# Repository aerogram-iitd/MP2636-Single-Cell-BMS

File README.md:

View this project on [CADLAB.io](https://cadlab.io/project/24484). 

# MP2636-Single-Cell-BMS
3A Switch Mode Battery Charger with System Boost using MP2636 from Monolithic Power

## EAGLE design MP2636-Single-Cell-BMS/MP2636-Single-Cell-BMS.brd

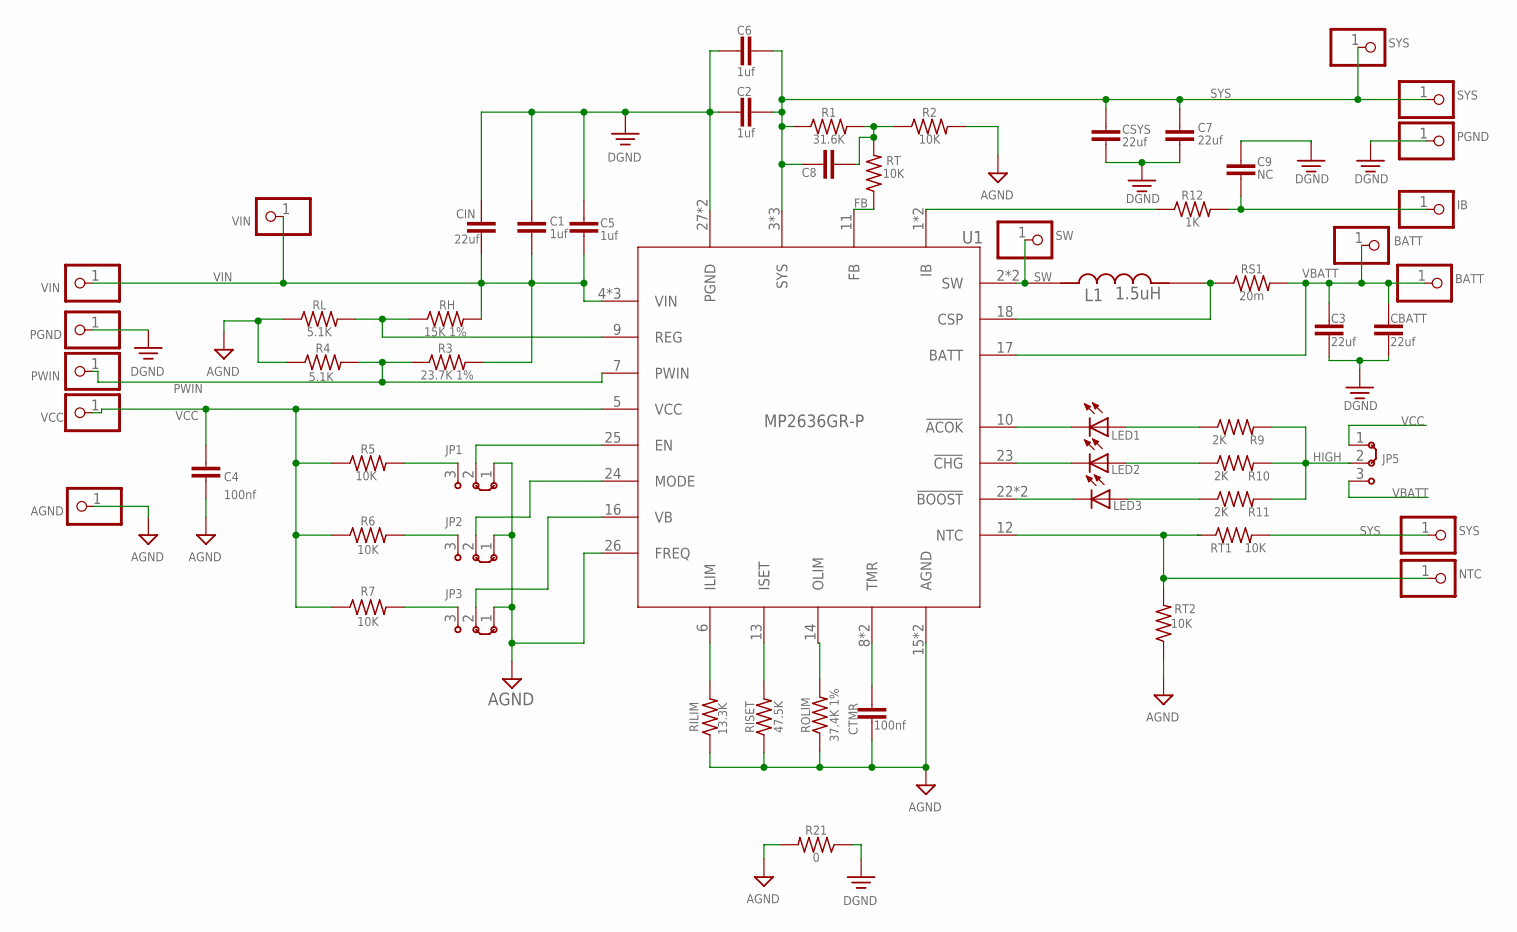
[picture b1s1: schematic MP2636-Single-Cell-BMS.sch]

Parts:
C1, C2, C5, C6: 1uf; CAPC2012X110
C3, C7: 22uf; CAPC2012X110
C4: 100nf; CAPC2012X110
C8: CAPC2012X110
C9: NC; CAPC2012X110
CBATT: 22uf; CAPC2012X110
CIN: 22uf; CAPC2012X110
CSYS: 22uf; CAPC2012X110
CTMR: 100nf; CAPC2012X110
F: SYS; 1X01
JP1, JP2, JP3, JP5: J2X2MM; 04C
JP4, JP9: VIN; 1X01
JP6, JP17: PGND; 1X01
JP7: PWIN; 1X01
JP8: VCC; 1X01
JP10: AGND; 1X01
JP11, JP18: SYS; 1X01
JP12: IB; 1X01
JP13, JP14: BATT; 1X01
JP15: NTC; 1X01
JP16: SW; 1X01
L1: 1.5uH; IND_LQH5BPN2R2NT0L
LED1, LED2, LED3: LEDCHIP-LED0805; CHIP-LED0805
R1: 31.6K; RESC2012X65
R2, R5, R6, R7: 10K; RESC2012X65
R3: 23.7K 1%; RESC2012X65
R4: 5.1K; RESC2012X65
R9, R10, R11: 2K; RESC2012X65
R12: 1K; RESC2012X65
R21: 0; RESC2012X65
RH: 15K 1%; RESC2012X65
RILIM: 13.3K; RESC2012X65
RISET: 47.5K; RESC2012X65
RL: 5.1K; RESC2012X65
ROLIM: 37.4K 1%; RESC2012X65
RS1: 20m; RESC2012X65
RT, RT1, RT2: 10K; RESC2012X65
U1: MP2636GR-P; IC_MP2636GR-P

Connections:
FB: RT.1, U1.11 (FB)
HIGH: JP5.2
IB: C9.1, JP12.1, R12.2
unnamed: R12.1, U1.1 (IB)
unnamed: JP1.3, R5.2
unnamed: JP1.2, U1.25 (EN)
unnamed: JP2.2, U1.24 (MODE)
unnamed: JP3.2, U1.16 (VB)
unnamed: JP2.3, R6.2
unnamed: JP3.3, R7.2
unnamed: RH.1, RL.2, U1.9 (REG)
unnamed: LED1.C, U1.10 (!ACOK)
unnamed: C8.2, R1.2, R2.1, RT.2
unnamed: LED2.C, U1.23 (!CHG)
unnamed: L1.2, RS1.1, U1.18 (CSP)
unnamed: LED3.C, U1.22 (!BOOST)
unnamed: LED1.A, R9.1
unnamed: LED2.A, R10.1
unnamed: LED3.A, R11.1
unnamed: R9.2, R10.2, R11.2
unnamed: RILIM.2, U1.6 (ILIM)
unnamed: RISET.2, U1.13 (ISET)
unnamed: ROLIM.2, U1.14 (OLIM)
unnamed: CTMR.1, U1.8 (TMR)
NTC: JP15.1, RT1.1, RT2.2, U1.12 (NTC)
PWIN: JP7.1, R3.1, R4.2, U1.7 (PWIN)
SW: JP16.1, L1.1, U1.2 (SW), U1.21 (SW)
SYS: C2.2, C6.2, C7.2, C8.1, CSYS.2, F.1, JP11.1, JP18.1, R1.1, RT1.2, U1.3 (SYS), U1.20 (SYS), U1.29 (SYS)
VBATT: C3.2, CBATT.2, JP5.3, JP13.1, JP14.1, RS1.2, U1.17 (BATT)
VCC: C4.1, JP5.1, JP8.1, R5.1, R6.1, R7.1, U1.5 (VCC)
VIN: C1.2, C5.2, CIN.2, JP4.1, JP9.1, R3.2, RH.2, U1.4 (VIN), U1.19 (VIN), U1.30 (VIN)

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
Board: 2 copper layers, 58 parts (0 on the bottom side), 32 nets, no tracks yet.

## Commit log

2021-06-25 Create LICENSE
2021-06-25 Blank project
2021-06-25 Backlink to CADLAB.io has been added.
2021-06-26 Frame added
2021-06-26 Library of MP2636 added
2021-06-26 MP2636 added
2021-06-26 Added Datasheet of MP2636
2021-06-26 Design Reference
2021-06-26 Library of inductor added
2021-06-26 Added jumper library
2021-06-30 Operation mode is added
2021-07-01 Input circuit is added
2021-07-01 Output circuit is added
2021-07-01 Battery circuit is added
2021-07-01 Indicator circuit is added
2021-07-01 NTC added
2021-07-01 Current limit circuit is added
2021-07-01 Updated names and values
2021-07-03 Updated MP2636 library
2021-07-05 Board file is generated
2021-07-05 Tentative component placements
